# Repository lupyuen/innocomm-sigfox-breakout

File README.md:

## InnoComm SN10-12 Sigfox Breakout Board

This breakout board connects your Arduino, Raspberry Pi and other devices to the Sigfox IoT network for low-power, long-range communications. The board uses the InnoComm SN10-12 module to connect to the Sigfox network. The interface between the device and the breakout board is based on SPI with 8 pins (3.3V, GND, CS, SDI, SDO, SCLK, AK, RST). A U.FL antenna and a Sigfox network subscription are required.

- Autodesk EAGLE board and schematic for InnoComm SN10-12 Sigfox Breakout board (Sigfox Zones RCZ2 and RCZ4) are in `innocomm-sigfox-breakout.brd` and `innocomm-sigfox-breakout.sch`

- The PCB design uses 2 layers: `Top` (layer 1), `Bottom` (layer 16).

- Formatted for Seeed Fusion PCB Assembly service, so that you may submit the files from this repository and order the breakout board fully assembled with the onboard components, including the InnoComm Sigfox module: <br>
  https://www.seeedstudio.com/fusion.html

- All components sourced from Seeed Open Parts Library (except for InnoComm module) for quicker PCB assembly by Seeed Fusion: <br>
  https://www.seeedstudio.com/opl.html

- Seeed Open Parts Library for Autodesk EAGLE: (only for the components used) <br>
  `Seeed-Capacitor.lbr` <br>
  `Seeed-Connector.lbr` <br>
  `Seeed-Inductor.lbr` <br>
  `Seeed-Resistor.lbr`
  
- SparkFun Library for Autodesk EAGLE was used for general symbols and components: <br>
  `SparkFun-Aesthetics.lbr` <br>
  `SparkFun-Boards.lbr` <br>
  `SparkFun-Connectors.lbr` <br>
  `SparkFun-PowerSymbols.lbr` <br>

- PCB layout was validated in Autodesk EAGLE with the Seeed Fusion Design Rules `SeeedStudio_2layer_DRU_no_angle_20140221.dru`

- PCB design was exported from Autodesk EAGLE to Seeed Fusion in Gerber RS-274X and Excellon (drill) formats using the CAM Processor Job `Seeed_Gerber_Generater_2-layer.cam`. To export:

  1. In EAGLE Board Editor, click `File → CAM Processor`

  1. At the top of the `CAM Processor` window, click the `Load Job File` icon.  Click `New CAM Job`.

  1. Click `Open CAM File`. Select `Seeed_Gerber_Generater_2-layer.cam`.

  1. Click `Export As ZIP`

  1. Under `Gerber → Options → Output Type`, select `Gerber RS-274X`.

  1. Click `Process Job`.  This creates a ZIP file that may be uploaded directly to Seeed Fusion.

- To export the Bill Of Materials (BOM) for uploading to Seeed Fusion: 

  1. In EAGLE Board Editor, click `File → Export Partlist`. Enter `partlist.csv` as the filename.

  1. We will use the first 2 columns of `partlist.csv`: <br>
      `Part:` Contains the `Designator` e.g. `C1`<br>
      `Value:` Contains 3 values - `Description` / `Manufacturer Part Number` / `SKU` (i.e. the Seeed Open Parts Library SKU number) like this: `33pf / CC0402JRNPO9BN330 / 302010000` <br>

  1. Open the file `innocomm-sigfox-breakout-bom.csv` in Excel. Populate the 3 columns:
      `Designator`, `Manufacturer Part Number`, `Quantity` like this:
      ```
      Designator,Manufacturer Part Number,Quantity
      C1,CC0402JRNPO9BN330,1
      C2,TAJC476K006RNJ,1
      U1,SN10-12,1
      ...
      ```
      We will provide a URL for Seeed Fusion to source for the InnoComm SN10-12 module.

  1. Save the CSV file for uploading to Seeed Fusion.  Check `innocomm-sigfox-breakout-bom.csv` for the BOM that I have submitted to Seeed Fusion.

## Seeed Fusion PCB Manufacturing and Assembly

Order submitted to Seeed Fusion for PCB manufacturing and assembly at https://www.seeedstudio.com/fusion_pcb.html:

1. `innocomm-sigfox-breakout_YYYY-MM-DD.zip`: PCB design in Gerber RS-274X and Excellon (drill) formats

1. PCB Specifications:

    |     |               |       |
    | ---:| ------------- | ----- |
    | 1.  | Base Material | `FR-4 TG130` |
    | 3.  | No. of Layers | `2 layers` |
    | 2.  | PCB Dimensions | `25.4 mm * 28.5mm` |
    | 4.  | PCB Quantity | _(Enter quantity)_ |
    | 5.  | No. of Different Designs | `1` |
    | 6.  | PCB Thickness | `1.6` |
    | 7.  | PCB Color | `Green` |
    | 8.  | Surface Finish | `HASL` |
    | 9.  | Minimum Solder Mask Dam | `0.1mm` |
    | 10. | Copper Weight | `1oz.` |
    | 11. | Minimum Drill Hole Size | `0.3mm` <br> (In EAGLE Board Editor, click <br> `Tools → Statistics → Drill / Hole → VIA Drill`) |
    | 12. | Trace Width / Spacing | `4/4 mil` <br> (In EAGLE Board Editor, click <br> `Tools → Statistics → Board → Minor → Wire Width`) |
    | 13. | Blind or Buried Vias | `No` |
    | 14. | Plated Half-holes / Castellated Holes | `No` |
    | 15. | Impedance Control | `No` |

1. `innocomm-sigfox-breakout-bom.csv`: PCB Assembly Bill Of Materials (BOM) for Sigfox Zones RCZ4 and RCZ4<br>

1. Link provided to Seeed Fusion for sourcing InnoComm SN10-12: <br>																									
    `https://www.arrow.com/zh-cn/products/sn10-12/innocomm-mobile-technology-corporation`

## References

1. Original PCB design for Wisol Sigfox Breakout Board: <br>
  https://github.com/lupyuen/Wisol-WSSFM10R-Sigfox-Breakout/tree/master/Hardware
  
1. Why I created the breakout board: <br>
  https://medium.com/@ly.lee/making-my-first-ever-pcb-with-seeed-fusion-pcb-assembly-service-9af5736016b3
  
1. List of all Sigfox Zones and the countries covered: <br>
  http://makers.sigfox.com/about/

1. _"InnoComm SN10-12 SIGFOX Module Product Specification"_: Available from InnoComm website upon registration.

1. _"Wisol WSSFM10R H/W Design Guide"_: For ESD protection circuit. Available from Wisol website upon registration.

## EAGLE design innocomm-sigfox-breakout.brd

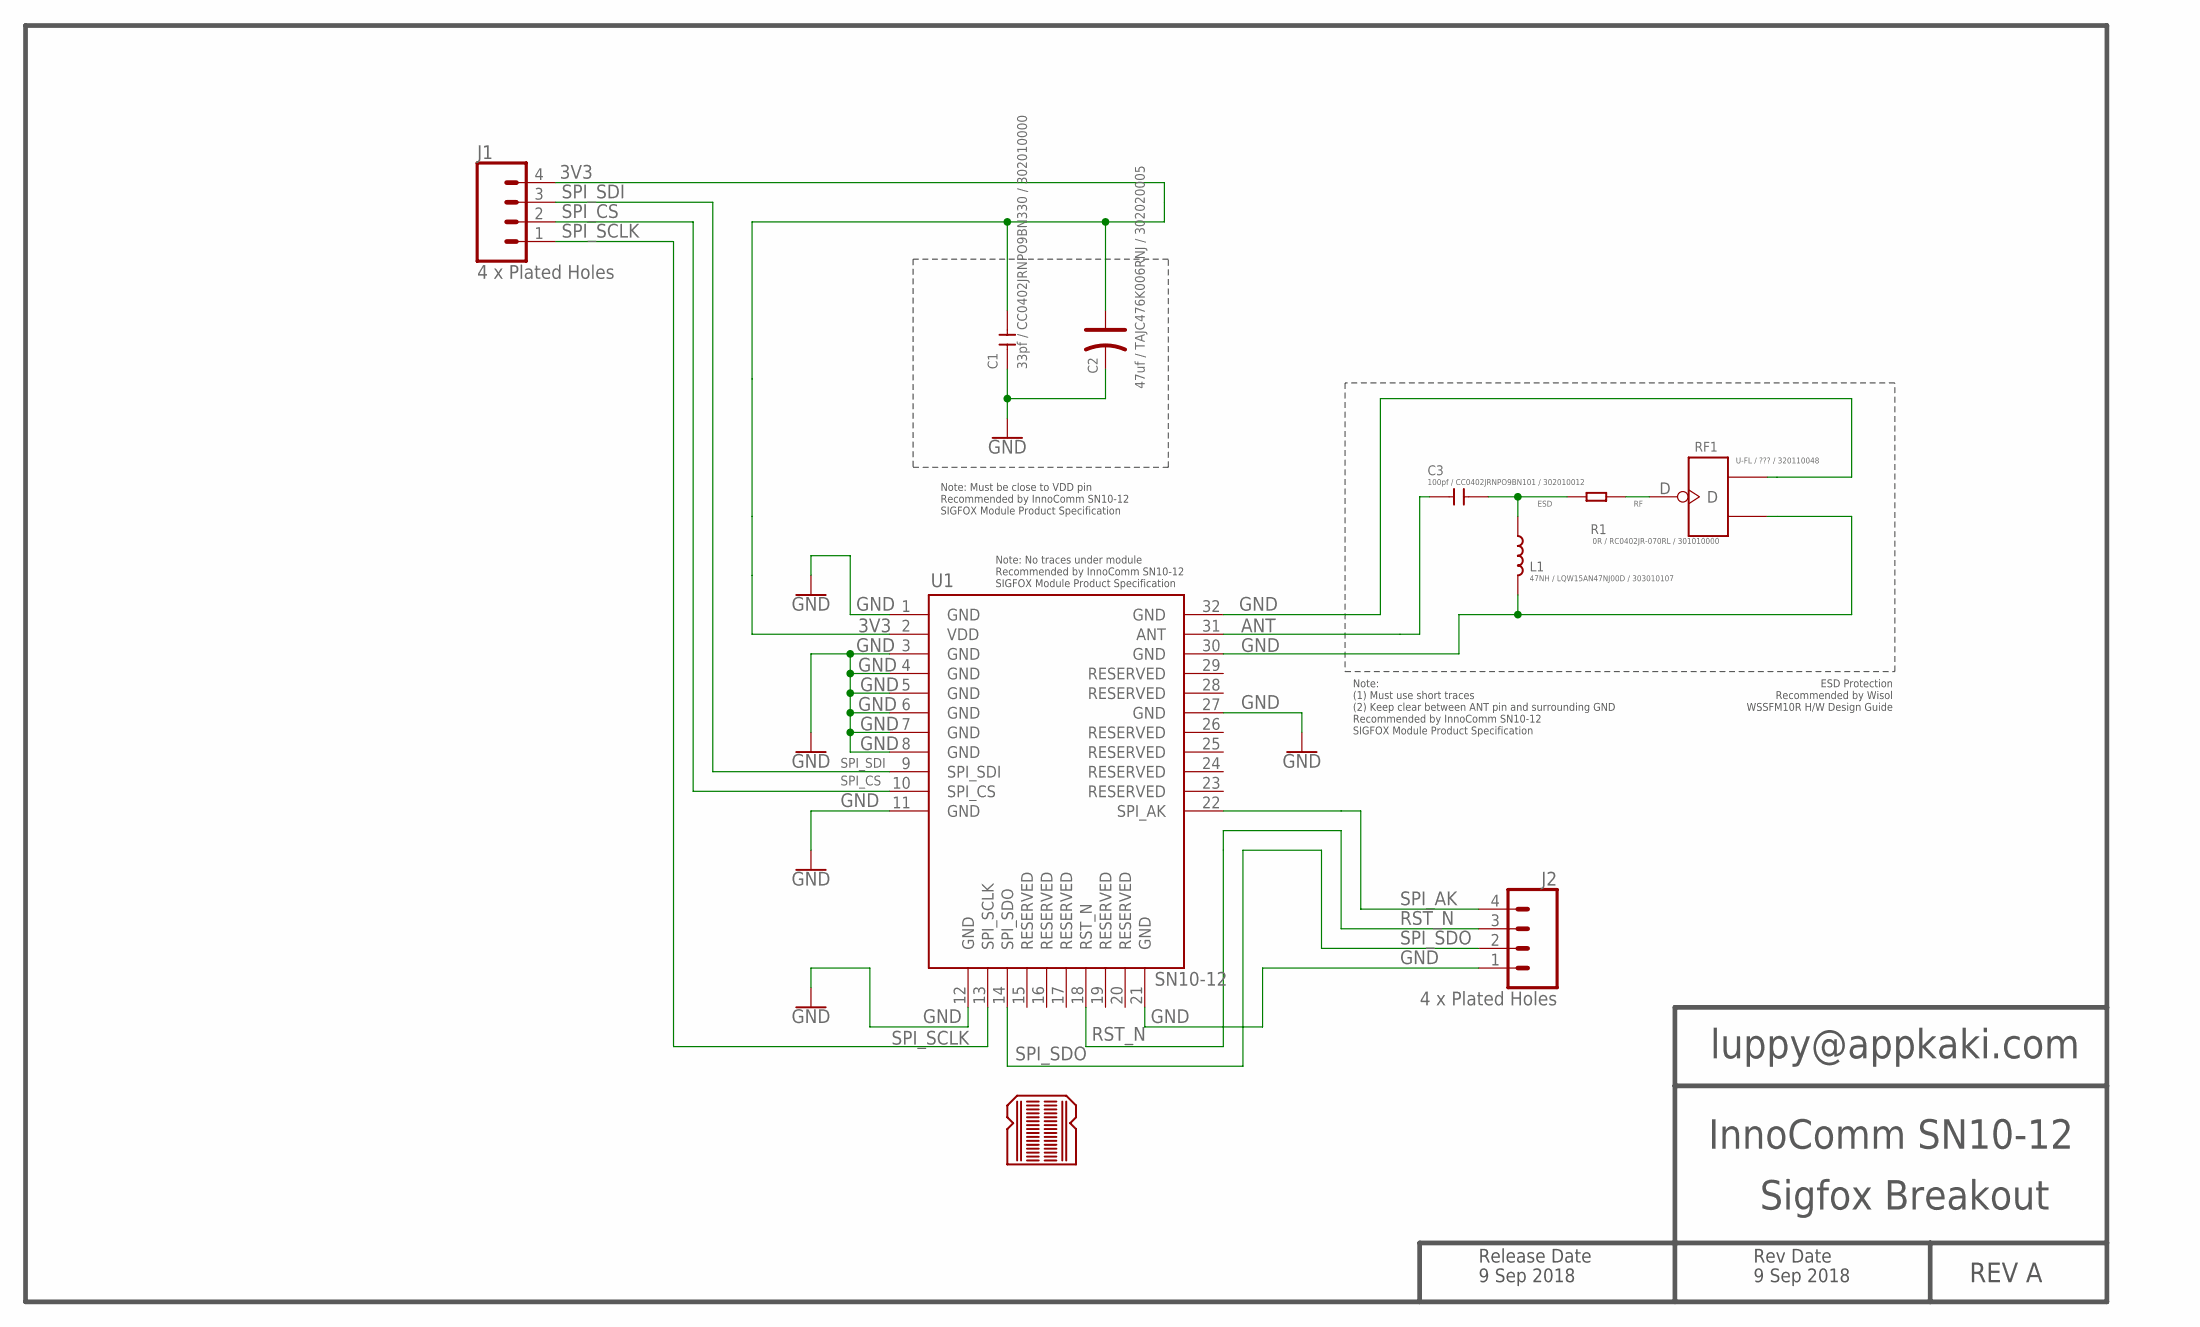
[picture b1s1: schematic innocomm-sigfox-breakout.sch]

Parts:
BREADBRD1: BREADBOARD_PATTERN; BREADBOARD_SPACING
C1: 33pf / CC0402JRNPO9BN330 / 302010000; C0402
C2: 47uf / TAJC476K006RNJ / 302020005; AVX-A; MPN TAJC476K006RNJ
C3: 100pf / CC0402JRNPO9BN101 / 302010012; C0402
J1, J2: 4 x Plated Holes; 1X04
L1: 47NH / LQW15AN47NJ00D / 303010107; L0402; MPN LQW15AN47NJ00D
R1: 0R / RC0402JR-070RL / 301010000; R0402
RF1: U-FL / ??? / 320110048; U-FL3P-SMD-2.6X2.6X1.0MM
U1: SN10-12; INNOCOMM-SN10-12; MPN SN10-12

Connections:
3V3: C1.2, C2.+, J1.4, U1.2 (VDD)
ANT: C3.1, U1.31 (ANT)
ESD: C3.2, L1.1, R1.1
GND: C1.1, C2.-, J2.1, L1.2, RF1.GND1, RF1.GND2, U1.1 (GND), U1.3 (GND), U1.4 (GND), U1.5 (GND), U1.6 (GND), U1.7 (GND), U1.8 (GND), U1.11 (GND), U1.12 (GND), U1.21 (GND), U1.27 (GND), U1.30 (GND), U1.32 (GND)
RF: R1.2, RF1.D
RST_N: J2.3, U1.18 (RST_N)
SPI_AK: J2.4, U1.22 (SPI_AK)
SPI_CS: J1.2, U1.10 (SPI_CS)
SPI_SCLK: J1.1, U1.13 (SPI_SCLK)
SPI_SDI: J1.3, U1.9 (SPI_SDI)
SPI_SDO: J2.2, U1.14 (SPI_SDO)

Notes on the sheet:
luppy@appkaki.com
InnoComm SN10-12
REV A
Sigfox Breakout
Release Date
9 Sep 2018
Rev Date
Note: Must be close to VDD pin Recommended by InnoComm SN10-12 SIGFOX Module Product Specification
Note: (1) Must use short traces (2) Keep clear between ANT pin and surrounding GND Recommended by InnoComm SN10-12 SIGFOX Module Product Specification
Note: No traces under module Recommended by InnoComm SN10-12 SIGFOX Module Product Specification
ESD Protection Recommended by Wisol WSSFM10R H/W Design Guide

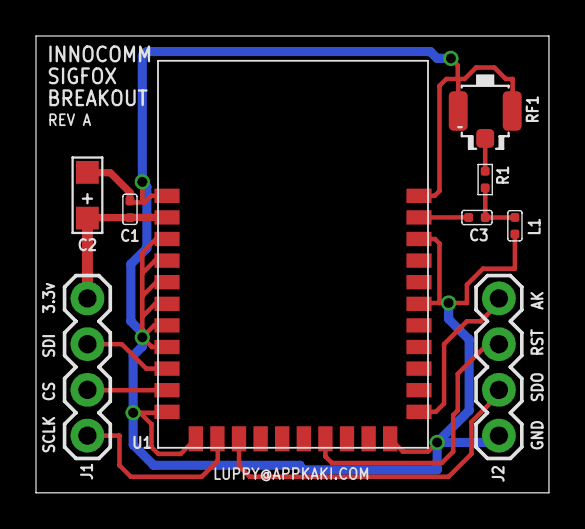
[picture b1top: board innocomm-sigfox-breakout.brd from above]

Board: 2 copper layers, 28.5 x 25.4 mm, 10 parts (0 on the bottom side), 11 nets.

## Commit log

2018-09-09 Order submitted to Seeed Fusion

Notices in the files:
parts and their libraries:
SparkFun-Connectors: Licensing: Creative Commons ShareAlike 4.0 International - https://creativecommons.org/licenses/by-sa/4.0
